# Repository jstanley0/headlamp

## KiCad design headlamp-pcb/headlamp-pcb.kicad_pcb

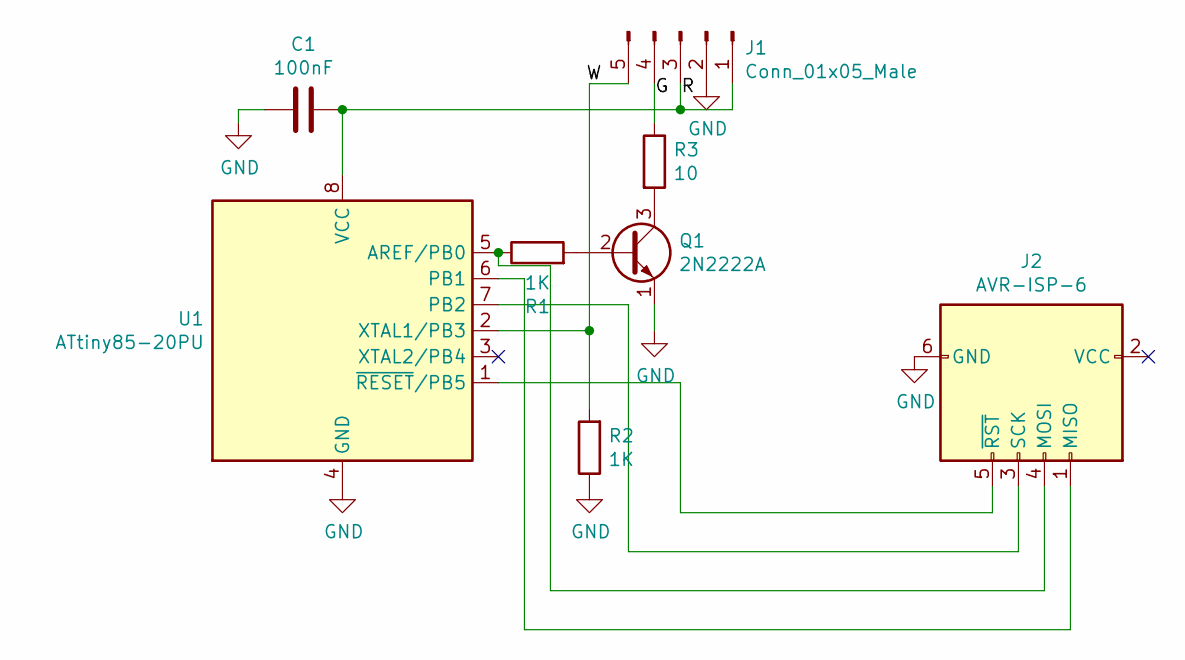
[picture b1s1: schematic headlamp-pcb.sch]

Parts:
C1: 100nF; C_Disc_D3.4mm_W2.1mm_P2.50mm
J1: Conn_01x05_Male; PinHeader_1x05_P2.54mm_Vertical
J2: AVR-ISP-6; PinHeader_2x03_P2.54mm_Vertical
Q1: 2N2222A; TO-92_Inline_Wide
R1, R2: 1K; R_Axial_DIN0204_L3.6mm_D1.6mm_P2.54mm_Vertical
R3: 10; R_Axial_DIN0204_L3.6mm_D1.6mm_P2.54mm_Vertical
U1: ATtiny85-20PU; DIP-8_W7.62mm

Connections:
/G: J1.4, R3.1
/R: C1.1, J1.1, J1.3, U1.8 (VCC)
/W: J1.5, R2.2, U1.2 (XTAL1/PB3)
GND: C1.2, J1.2, J2.6 (GND), Q1.1 (E), R2.1, U1.4 (GND)
unnamed: J2.1 (MISO), U1.6 (PB1)
unnamed: J2.3 (SCK), U1.7 (PB2)
unnamed: J2.4 (MOSI), R1.1, U1.5 (AREF/PB0)
unnamed: J2.5 (~RST), U1.1 (~RESET~/PB5)
unnamed: Q1.2 (B), R1.2
unnamed: Q1.3 (C), R3.2

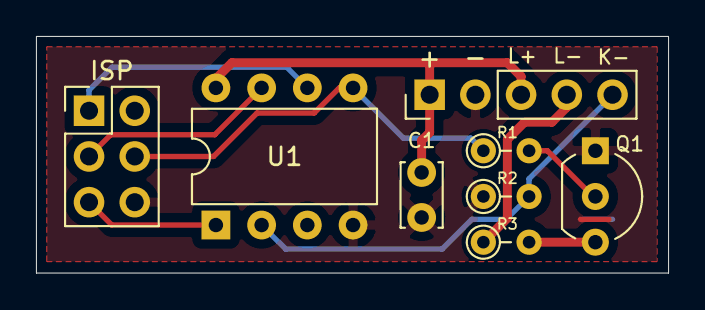
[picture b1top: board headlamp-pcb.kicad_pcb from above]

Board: 2 copper layers, 35.1 x 13.1 mm, 8 parts (0 on the bottom side), 10 nets.

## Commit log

2022-09-04 initial commit
    this is still thoroughly broken but it does prove some concepts
    things to fix:
    - it starts in LOW, not OFF, and I don't know why
    - holding the button to power off works, except that releasing
    the button wakes it up again and I don't know why
    - the fade functionality is thoroughly broken (and blocks I/O
2022-09-05 fix poweroff issue
    turns out there is an important difference between sleep_mode()
    and sleep_cpu(). sync_sleep() used the former and this cleared
    the sleep enable bit and prevented the latter from working again.
    so just use sleep_mode() everywhere
    also fix double-input on wakeup, which is probably why we never
    saw low-brightness mode before
2022-09-06 fix hold issue
    the bug was hold time was cumulative for holds not long enough
    to meet the threshold. need to reset the hold counter. the dumb
    thing is I have fixed this bug before in other avr projects :P
2022-09-06 remove pwm "off" state
    0 isn't off; we can't get a full off without using inverting
    fast PWM mode, but we have no reason to have the light off
    without powering down the micro
    also we can't fade between off and minimum, because it's
    literally the minimum duty cycle
    so just use 0-3 to mean low, med, hi, zomgblinding and drop
2022-09-06 fade faster to/from max
    and simplify the logic a little
    I still refuse to make it understandable or robust
2022-09-06 increase PWM refresh rate
    it was 61Hz (1MHz / 256 / 64) but this was visually noticeable
    since we're on hardware PWM there's probably no reason not to
    just drop the timer clock divider to 1/8 (which gets us 488Hz)
2022-09-07 prevent spurious power-on events
    I found that simply taking the headlamp off my head generates
    a pin-change interrupt pretty consistently. turn off headlamp,
    take it off my head, and it immediately turns itself back on.
    whoops.
    static electricity from my hair maybe? 10K pulldown resistor
    not sufficient? come to think of it, the circuit this replaces
2022-09-07 power off after 20 minutes of inactivity
    the spurious power-on events (that the last commit seems to have
    solved) make me worry about this thing killing itself in my bag.
    so I decided to make it power down after 20 minutes with no
    button presses.
    this jibes with my use case (short bursts of a red light while
    switching eyepieces or changing lenses) but if you use this
2022-09-08 add schematic and PCB
